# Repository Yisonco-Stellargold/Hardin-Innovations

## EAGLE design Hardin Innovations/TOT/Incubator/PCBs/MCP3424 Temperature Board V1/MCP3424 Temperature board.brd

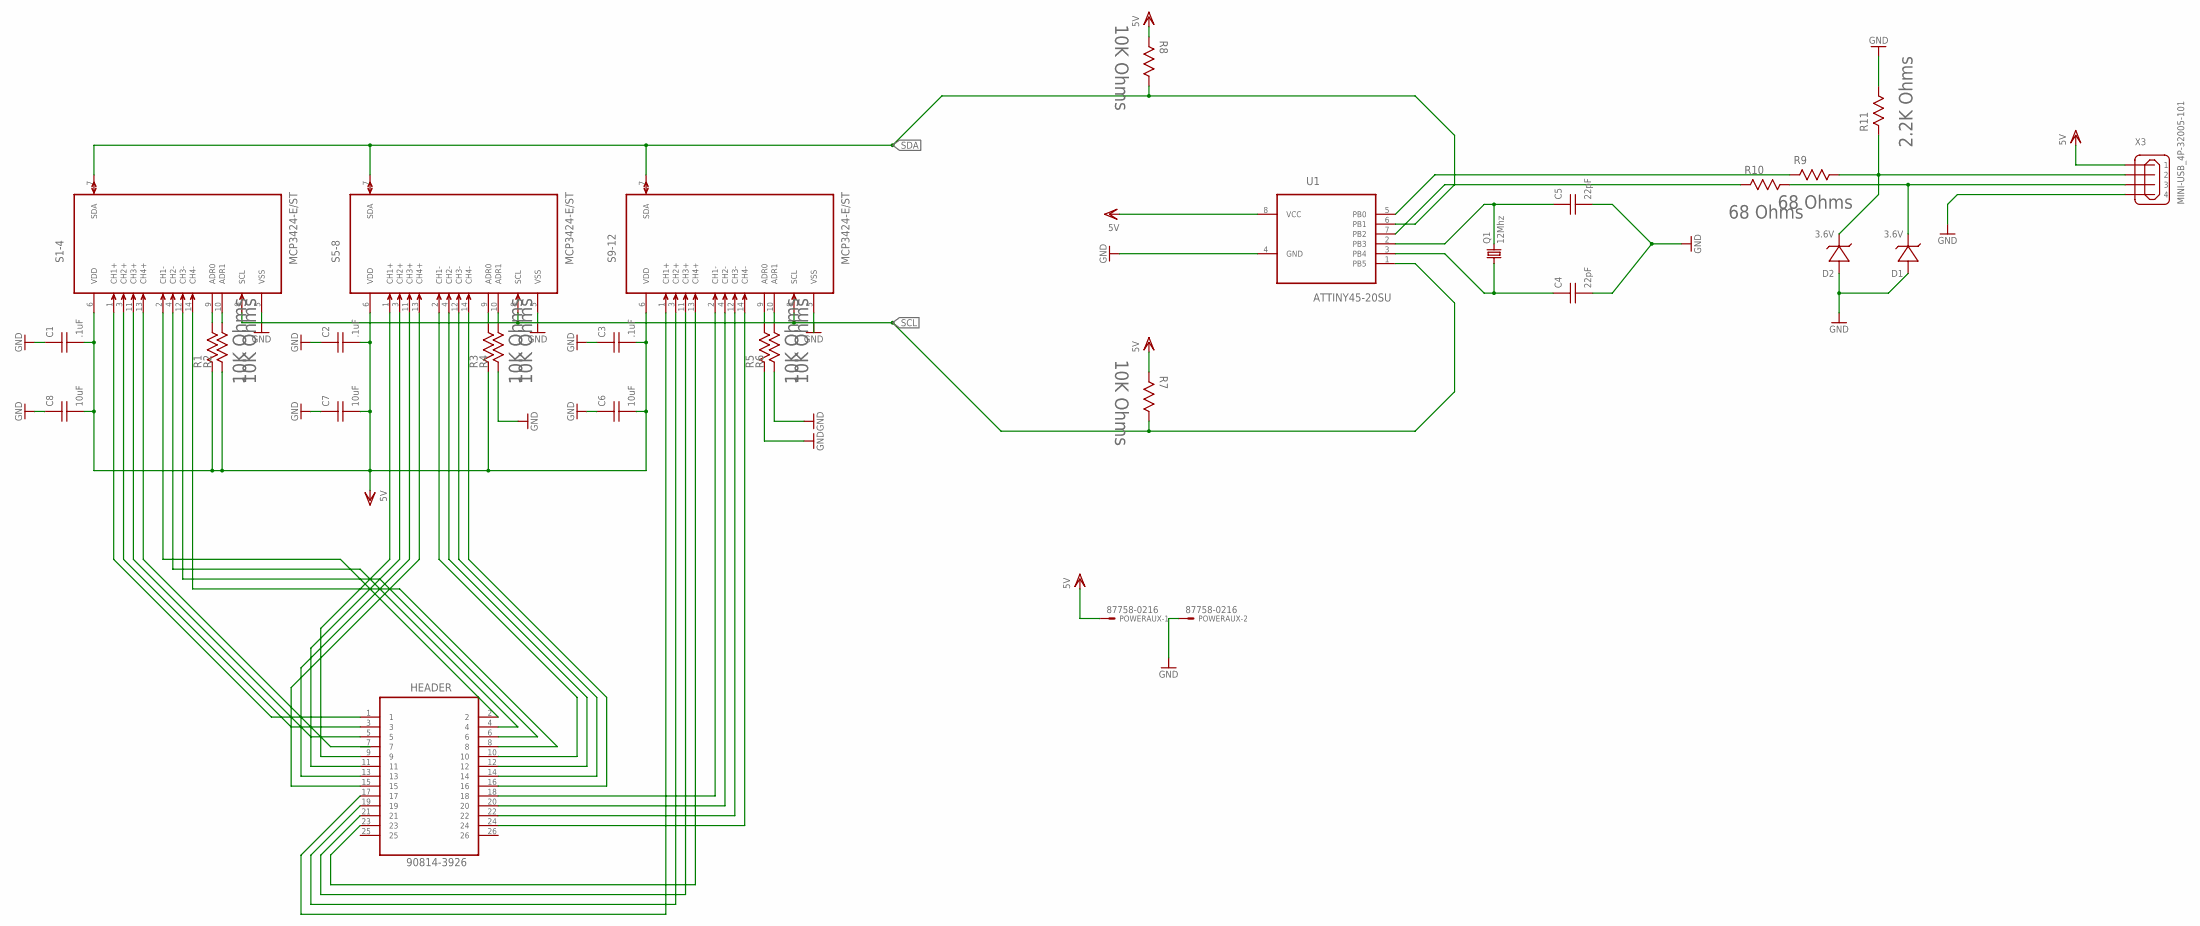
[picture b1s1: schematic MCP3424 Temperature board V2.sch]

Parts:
C1, C2, C3: .1uF; C0805; MPN C0805C104Z3VACTU
C4, C5: 22pF; C0805; MPN CC0805JRNPO9BN220
C6, C7, C8: 10uF; C0805; MPN NOJP106M006RWJ
D1, D2: 3.6V; SOD123; MPN MM3Z3V6T1G
HEADER: 90814-3926; MOLEX_90814-3926; MPN 50-57-9002
POWERAUX: 87758-0216
Q1: 12Mhz; HC49UP; MPN ABLS-12.000MHZ-B2-T
R1, R2, R3, R4, R5, R6, R7, R8: 10K Ohms; RESC2013X65N; MPN CRCW080510K0JNEA
R9, R10: 68 Ohms; RESC2013X65N; MPN ERJ-B3BFR68V
R11: 2.2K Ohms; RESC2013X65N; MPN CRCW08052K20FKEA
S1-4, S5-8, S9-12: MCP3424-E/ST; SOP65P640X120-14N
U1: ATTINY45-20SU; SOIC127P798X216-8N
X3: MINI-USB_4P-32005-101; 32005-101; MPN 651005136421

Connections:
GND: C1.1 (A), C2.1 (A), C3.1 (A), C4.2 (B), C5.2 (B), C6.1 (A), C7.1 (A), C8.1 (A), D1.A (+), D2.A (+), POWERAUX.2, R4.2, R5.2, R6.2, R11.1, S1-4.5 (VSS), S5-8.5 (VSS), U1.4 (GND), X3.4; also elsewhere on the board
unnamed: HEADER.1, S1-4.1 (CH1+)
unnamed: R1.1, S1-4.9 (ADR0)
unnamed: R2.1, S1-4.10 (ADR1)
unnamed: R3.1, S5-8.9 (ADR0)
unnamed: R4.1, S5-8.10 (ADR1)
unnamed: HEADER.3, S1-4.3 (CH2+)
unnamed: R5.1, S9-12.9 (ADR0)
unnamed: R6.1, S9-12.10 (ADR1)
unnamed: HEADER.5, S1-4.11 (CH3+)
unnamed: HEADER.2, S1-4.2 (CH1-)
unnamed: HEADER.4, S1-4.4 (CH2-)
unnamed: HEADER.6, S1-4.12 (CH3-)
unnamed: HEADER.8, S1-4.14 (CH4-)
unnamed: HEADER.9, S5-8.1 (CH1+)
unnamed: HEADER.11, S5-8.3 (CH2+)
unnamed: HEADER.13, S5-8.11 (CH3+)
unnamed: HEADER.15, S5-8.13 (CH4+)
unnamed: HEADER.10, S5-8.2 (CH1-)
unnamed: HEADER.16, S5-8.14 (CH4-)
unnamed: HEADER.14, S5-8.12 (CH3-)
unnamed: HEADER.12, S5-8.4 (CH2-)
unnamed: HEADER.17, S9-12.1 (CH1+)
unnamed: HEADER.19, S9-12.3 (CH2+)
unnamed: HEADER.23, S9-12.13 (CH4+)
unnamed: HEADER.21, S9-12.11 (CH3+)
unnamed: HEADER.24, S9-12.14 (CH4-)
unnamed: HEADER.22, S9-12.12 (CH3-)
unnamed: HEADER.20, S9-12.4 (CH2-)
unnamed: HEADER.18, S9-12.2 (CH1-)
unnamed: R9.2, U1.5 (PB0)
unnamed: R10.2, U1.7 (PB2)
unnamed 34: D2.C (-), R9.1, R11.2, X3.2; also elsewhere on the board
unnamed 35: D1.C (-), R10.1, X3.3; also elsewhere on the board
unnamed: C4.1 (A), Q1.1, U1.3 (PB4)
unnamed: C5.1 (A), Q1.2, U1.2 (PB3)
SCL: R7.1, S1-4.8 (SCL), S5-8.8 (SCL), S9-12.8 (SCL), U1.1 (PB5)
SDA: R8.1, S1-4.7 (SDA), S5-8.7 (SDA), S9-12.7 (SDA), U1.6 (PB1)
VDD: C1.2 (B), C2.2 (B), C3.2 (B), C6.2 (B), C7.2 (B), C8.2 (B), POWERAUX.1, R1.2, R2.2, R3.2, R7.2, R8.2, S1-4.6 (VDD), S5-8.6 (VDD), S9-12.6 (VDD), U1.8 (VCC), X3.1

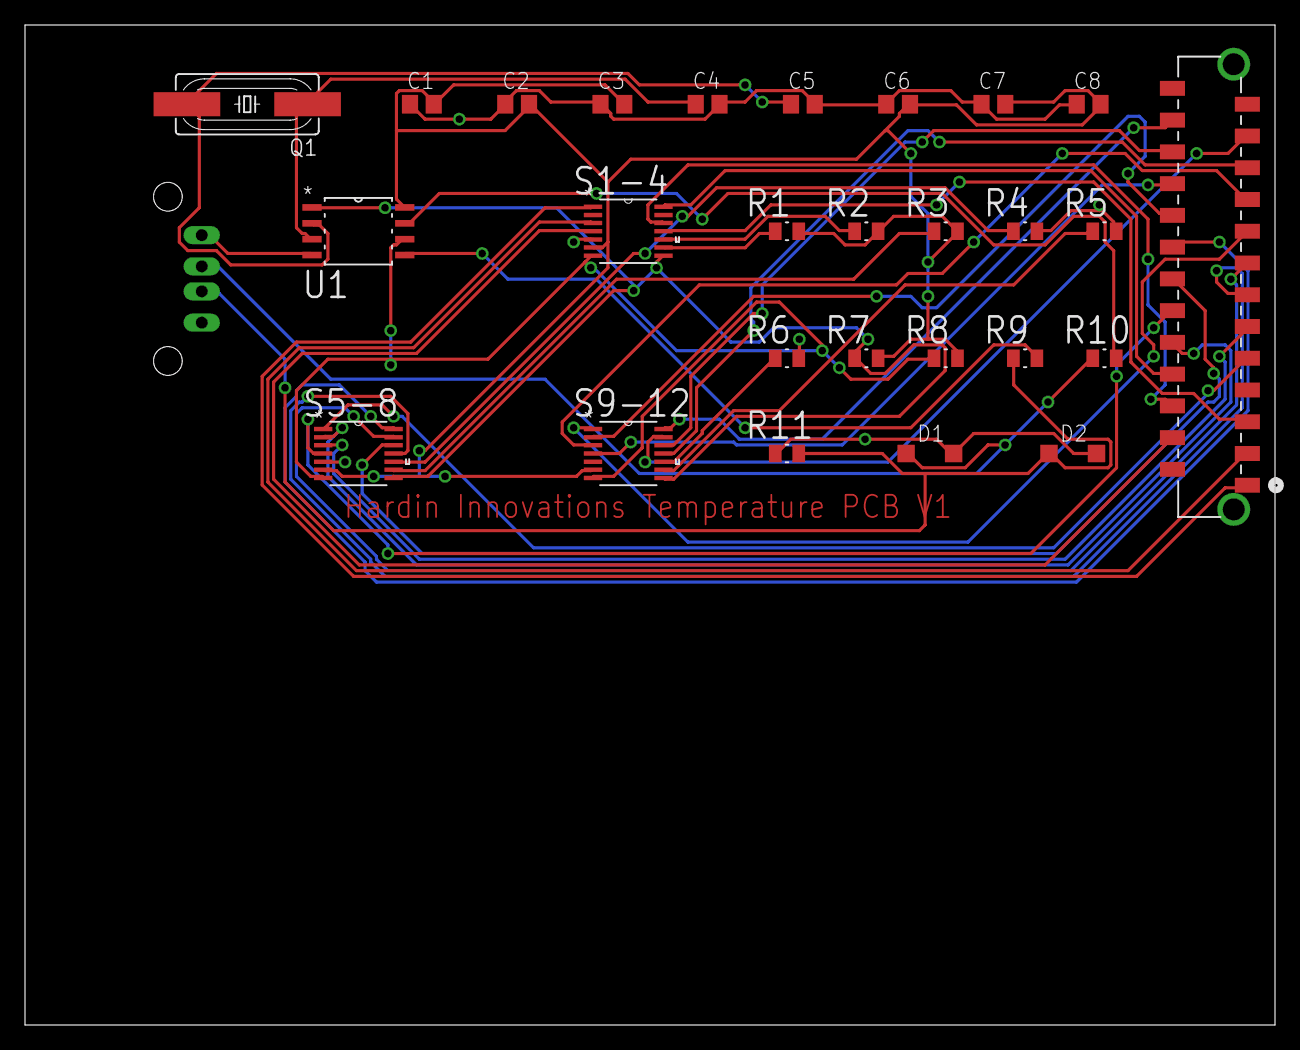
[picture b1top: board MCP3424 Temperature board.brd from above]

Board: 2 copper layers, 100.0 x 80.0 mm, 28 parts (1 on the bottom side), 39 nets.

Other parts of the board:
X1: 5V; PN87520

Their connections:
GND: X1.4; also elsewhere on the board
unnamed 34: X1.2; also elsewhere on the board
unnamed 35: X1.3; also elsewhere on the board

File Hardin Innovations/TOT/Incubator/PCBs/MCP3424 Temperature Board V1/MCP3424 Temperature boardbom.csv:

"Part";"Value";"Device";"Package";"Description";"MF";"MPN";"OC_FARNELL";"OC_NEWARK";"PACKAGE";"SUPPLIER";"TOLERANCE";"VALUE";"WATTAGE";
"C1";".1uF";"CAP";"C0805";"Capacitor";"";"";"";"";"";"";"";"";"";
"C2";".1uF";"CAP";"C0805";"Capacitor";"";"";"";"";"";"";"";"";"";
"C3";".1uF";"CAP";"C0805";"Capacitor";"";"";"";"";"";"";"";"";"";
"C4";"22pF";"CAP";"C0805";"Capacitor";"";"";"";"";"";"";"";"";"";
"C5";"22pF";"CAP";"C0805";"Capacitor";"";"";"";"";"";"";"";"";"";
"C6";"10uF";"CAP";"C0805";"Capacitor";"";"";"";"";"";"";"";"";"";
"C7";"10uF";"CAP";"C0805";"Capacitor";"";"";"";"";"";"";"";"";"";
"C8";"10uF";"CAP";"C0805";"Capacitor";"";"";"";"";"";"";"";"";"";
"D1";"3.6V";"ZENER";"SOD123";"Zener Diode";"";"";"";"";"";"";"";"";"";
"D2";"3.6V";"ZENER";"SOD123";"Zener Diode";"";"";"";"";"";"";"";"";"";
"HEADER";"90814-3926";"90814-3926";"MOLEX_90814-3926";"CONN HEADER 26POS 1.27MM SMD GOLD";"";"90814-3926";"1757067";"34R6253";"CONN-26POS";"Molex";"";"";"";
"Q1";"12Mhz";"CRYSTALHC49UP";"HC49UP";"CRYSTAL";"";"";"unknown";"unknown";"";"";"";"";"";
"R1";"10K Ohms";"P0805Z1002WNT0079";"RESC2013X65N";"RESISTOR, 0805";"";"P0805Z1002WNT0079";"1791003";"70R0101";"";"Vishay";"± 0.05 %";"10K Ohms";"200mW";
"R2";"10K Ohms";"P0805Z1002WNT0079";"RESC2013X65N";"RESISTOR, 0805";"";"P0805Z1002WNT0079";"1791003";"70R0101";"";"Vishay";"± 0.05 %";"10K Ohms";"200mW";
"R3";"10K Ohms";"P0805Z1002WNT0079";"RESC2013X65N";"RESISTOR, 0805";"";"P0805Z1002WNT0079";"1791003";"70R0101";"";"Vishay";"± 0.05 %";"10K Ohms";"200mW";
"R4";"10K Ohms";"P0805Z1002WNT0079";"RESC2013X65N";"RESISTOR, 0805";"";"P0805Z1002WNT0079";"1791003";"70R0101";"";"Vishay";"± 0.05 %";"10K Ohms";"200mW";
"R5";"10K Ohms";"P0805Z1002WNT0079";"RESC2013X65N";"RESISTOR, 0805";"";"P0805Z1002WNT0079";"1791003";"70R0101";"";"Vishay";"± 0.05 %";"10K Ohms";"200mW";
"R6";"10K Ohms";"P0805Z1002WNT0079";"RESC2013X65N";"RESISTOR, 0805";"";"P0805Z1002WNT0079";"1791003";"70R0101";"";"Vishay";"± 0.05 %";"10K Ohms";"200mW";
"R7";"10K Ohms";"P0805Z1002WNT0079";"RESC2013X65N";"RESISTOR, 0805";"";"P0805Z1002WNT0079";"1791003";"70R0101";"";"Vishay";"± 0.05 %";"10K Ohms";"200mW";
"R8";"10K Ohms";"P0805Z1002WNT0079";"RESC2013X65N";"RESISTOR, 0805";"";"P0805Z1002WNT0079";"1791003";"70R0101";"";"Vishay";"± 0.05 %";"10K Ohms";"200mW";
"R9";"68 Ohms";"P0805Z1002WNT0079";"RESC2013X65N";"RESISTOR, 0805";"";"P0805Z1002WNT0079";"1791003";"70R0101";"";"Vishay";"± 0.05 %";"10K Ohms";"200mW";
"R10";"68 Ohms";"P0805Z1002WNT0079";"RESC2013X65N";"RESISTOR, 0805";"";"P0805Z1002WNT0079";"1791003";"70R0101";"";"Vishay";"± 0.05 %";"10K Ohms";"200mW";
"R11";"2.2K Ohms";"P0805Z1002WNT0079";"RESC2013X65N";"RESISTOR, 0805";"";"P0805Z1002WNT0079";"1791003";"70R0101";"";"Vishay";"± 0.05 %";"10K Ohms";"200mW";
"S1-4";"MCP3424-E/ST";"MCP3424-E/ST";"SOP65P640X120-14N";"Analog-to-Digital Converter";"";"MCP3424-E/ST";"1630423";"54M4872";"SOP-14";"Microchip";"";"";"";
"S5-8";"MCP3424-E/ST";"MCP3424-E/ST";"SOP65P640X120-14N";"Analog-to-Digital Converter";"";"MCP3424-E/ST";"1630423";"54M4872";"SOP-14";"Microchip";"";"";"";
"S9-12";"MCP3424-E/ST";"MCP3424-E/ST";"SOP65P640X120-14N";"Analog-to-Digital Converter";"";"MCP3424-E/ST";"1630423";"54M4872";"SOP-14";"Microchip";"";"";"";
"U1";"ATTINY45-20SU";"ATTINY45-20SU";"SOIC127P798X216-8N";"8-bit Microcontroller with 4 Bytes In-System Programmable Flash";"";"ATTINY45-20SU";"1288353";"23M5073";"SOIC-8";"Atmel";"";"";"";
"X1";"5V";"PN87520";"PN87520";"BERG USB connector";"";"";"unknown";"unknown";"";"";"";"";"";

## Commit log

2016-05-12 Add files via upload
    Initial Upload
